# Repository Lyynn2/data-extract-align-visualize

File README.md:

# Setup: Organizing Data

Most scripts have a variable at the beginning called `data_root_dir`.  This should point to a folder that is analogous to the AWS folder `ceti-data > raw > 2023-07-08`.  It should have a subfolder for each device that you want to use, which is named according to the device ID.  

If you want to use coda annotations, the root folder should have subfolders called `_coda_annotations_biology` and `_coda_annotations_haifa` with a CSV in each one; these might be available on AWS, and just in case they're also available [here](https://drive.google.com/drive/folders/1o6aclfZT1td0Xjm15IKLw7Pj57yaxBNU?usp=sharing).

If you want to use the scripts that use extracted files of drone data (`example_use_drone_data.py`, `drone_plot_gps.py`, `drone_plot_speed.py`), you can download the HDF5 files from [here](https://drive.google.com/drive/folders/1VRa-VetmZ5YfDLSZ_6jQgG1d_zl_QoxG?usp=drive_link).  You can then place each one in the relevant drone data subfolder of the data root folder, or adjust the filepaths at the top of the scripts.

# Examples of Extracting Timestamped Data

`example_get_audio_with_timestamps.py` 
- Will load audio data as a raw waveform or as a spectrogram
- Will load aligned timestamps for each audio sample.

`example_get_coda_annotations.py`
- Will load coda annotations from the biology and/or Haifa teams.
- Will provide click times, ICIs, whale indexes, etc. for each coda.
- Timestamps will be adjusted based on alignment offsets.
- **Link to coda annotations files:** [https://drive.google.com/drive/folders/1o6aclfZT1td0Xjm15IKLw7Pj57yaxBNU?usp=sharing](https://drive.google.com/drive/folders/1o6aclfZT1td0Xjm15IKLw7Pj57yaxBNU?usp=sharing)
  - Download the folders from the above link and place them in your root data directory alongside other folders downloaded from AWS.
  - For example, another folder within that root data directory is probably `DSWP-KASHMIR_MIXPRE6-1`
  - `_coda_annotations_biology` and `_coda_annotations_haifa` will be considered the device IDs for now.

`example_use_drone_data.py`
- Will load extracted metadata from HDF5 files.
- Includes GPS positions, altitude, estimated speed, and camera settings for each video frame.
- Includes aligned timestamps for each video frame.
- **Link to drone data files:** [https://drive.google.com/drive/folders/1VRa-VetmZ5YfDLSZ_6jQgG1d_zl_QoxG?usp=drive_link](https://drive.google.com/drive/folders/1VRa-VetmZ5YfDLSZ_6jQgG1d_zl_QoxG?usp=drive_link)
  - Download the two HDF5 files from the `Data and Code` folder. 

# Visualizing Data
`create_composite_video.py` **will create a video with synchronized visualizations from any desired combination of devices.**
  - The dictionary `composite_layout` defines which device streams should be visualized and how they should be arranged on the video.
  - The variables `output_video_start_time_str` and `output_video_duration_s` define the span of the video.

`drone_plot_gps.py` will create an animation of the drones' GPS paths.

 `drone_ploy_speed.py` will plot horizontal drone speed and stationary periods as estimated from the GPS positions.

# Notable Helpers

## Timestamps and Device Alignment

- To get an aligned start time of a file, you can call `adjust_start_time_s(get_time_s_from_filename(filepath), device_id)`
  - `helpers_data_extraction.py > get_time_s_from_filename()` will extract the start time of a file from the 13-digit epoch timestamp in the filename.  This timestamp is from the device clock (not aligned to other devices).
  - `helpers_synchronization.py > adjust_start_time_s()` will adjust a device-based start time to synchronize it with other devices.  Will look up the appropriate offset to add based on the device and the original start time.

- The dictionary `helpers_synchronization.py > epoch_offsets_toAdd_s` defines the manual synchronization offsets.  There may be a single offset per device, or a variable offset per device that changes throughout the expedition.  
  - These were manually defined by finding key frames throughout the data (typically frames when a blow just barely begins).  
  - The hydrophone offset was determined using two codas in file 280 that were also audible in videos.  The file `video_audio_alignment_plotting.py` will plot the waveforms at these codas to visualize the alignment.

- `helpers_various.py > time_s_to_str()` and `time_str_to_time_s()` convert between epoch time (seconds since January 1, 1970) and a human-readable timestamp string.  Note that `time_s_to_str` requires information about the local time zone; for the birthday data `timezone_offset_s = -14400` and `timezone_offset_str = '-0400'`.

## Extracting Timestamped Data
- `helpers_data_extraction.py` provides methods for getting video frames, images, audio waveforms, audio spectrograms, drone flight/camera data, and coda annotations with associated aligned timestamps: 
  - `get_timestamped_data_audioVideoImage()`
  - `get_timestamped_data_codas()` 
  - `get_timestamped_data_drones()` (but note that the HDF5 files mentioned above are recommended, since they include both aligned and original timestamps as well as other formatted fields)

## Subclasses for Faster Video Plotting and Writing

- `ImagePlot` is a custom plotting class to speed up plotting for video generation.  It builds plot images directly instead of using a plotting library, so it is fast for basic functions and does not require a dedicated export/render step to fetch an image of the plot.

- `ThreadedVideoWriter` is a video writer wrapper to speed up video writing.  It maintains a rolling buffer of frames to write and then performs the actual write in a dedicated thread, so your main code can continue working on synthesizing the next frame while the previous frame is being written.

# Python Setup/Installation

The code has so far been run with Python version `3.9.9`. Versions of notable packages that the code has currently been tested with are listed below:

**Image/Video**
- `pip install decord==0.6.0` for quickly loading video frames
- `pip install Pillow==9.1.0` for quickly loading images
- `pip install moviepy==1.0.3` for adding aligned audio to generated composite videos
- `pip install proglog==0.1.10` for controlling log outputs when adding audio to generated composite videos
- `pip install ffmpeg-python==0.2.0` and maybe `pip install ffmpegcv==0.3.7` for compressing output videos
- `pip install opencv-python==4.8.0.76` for drawing text and shapes on images

**Plotting**
- `pip install distinctipy==1.2.2` for generating unique plot colors
- `pip install matplotlib==3.5.1` for plotting drone data
- `pip install tilemapbase==0.4.7` for plotting maps with drone GPS data
- `pip install pyqtgraph==0.12.4` for plotting video/audio alignment graphs. May also be relevant: `pip install PyQt6==6.3.0`, `pip install PyQt6-Qt6==6.3.0`, `pip install PyQt6-sip==13.3.1`, `pip install PyOpenGL==3.1.6`

**Data/Math**
- `pip install numpy==1.23.5`
- `pip install h5py==3.1.0` and maybe `pip install h5py-cache==1.0` for storing/loading extracted drone data
- `pip install pandas==1.3.5` for downloading data from AWS
- `pip install scipy==1.9.1` for loading/processing audio files
- `pip install python-dateutil==2.8.2` for parsing timestamp strings
- `pip install pysrt==1.1.2` for extracting drone data from SRT files

**All of the above**
```
  pip install decord==0.6.0
  pip install Pillow==9.1.0
  pip install moviepy==1.0.3
  pip install proglog==0.1.10
  pip install ffmpeg-python==0.2.0
  pip install ffmpegcv==0.3.7
  pip install opencv-python==4.8.0.76
  pip install distinctipy==1.2.2
  pip install matplotlib==3.5.1
  pip install tilemapbase==0.4.7
  pip install pyqtgraph==0.12.4
  #pip install PyQt6==6.3.0
  #pip install PyQt6-Qt6==6.3.0
  #pip install PyQt6-sip==13.3.1
  #pip install PyOpenGL==3.1.6
  pip install numpy==1.23.5
  pip install h5py==3.1.0
  pip install h5py-cache==1.0
  pip install pandas==1.3.5
  pip install scipy==1.9.1
  pip install python-dateutil==2.8.2
  pip install pysrt==1.1.2
```

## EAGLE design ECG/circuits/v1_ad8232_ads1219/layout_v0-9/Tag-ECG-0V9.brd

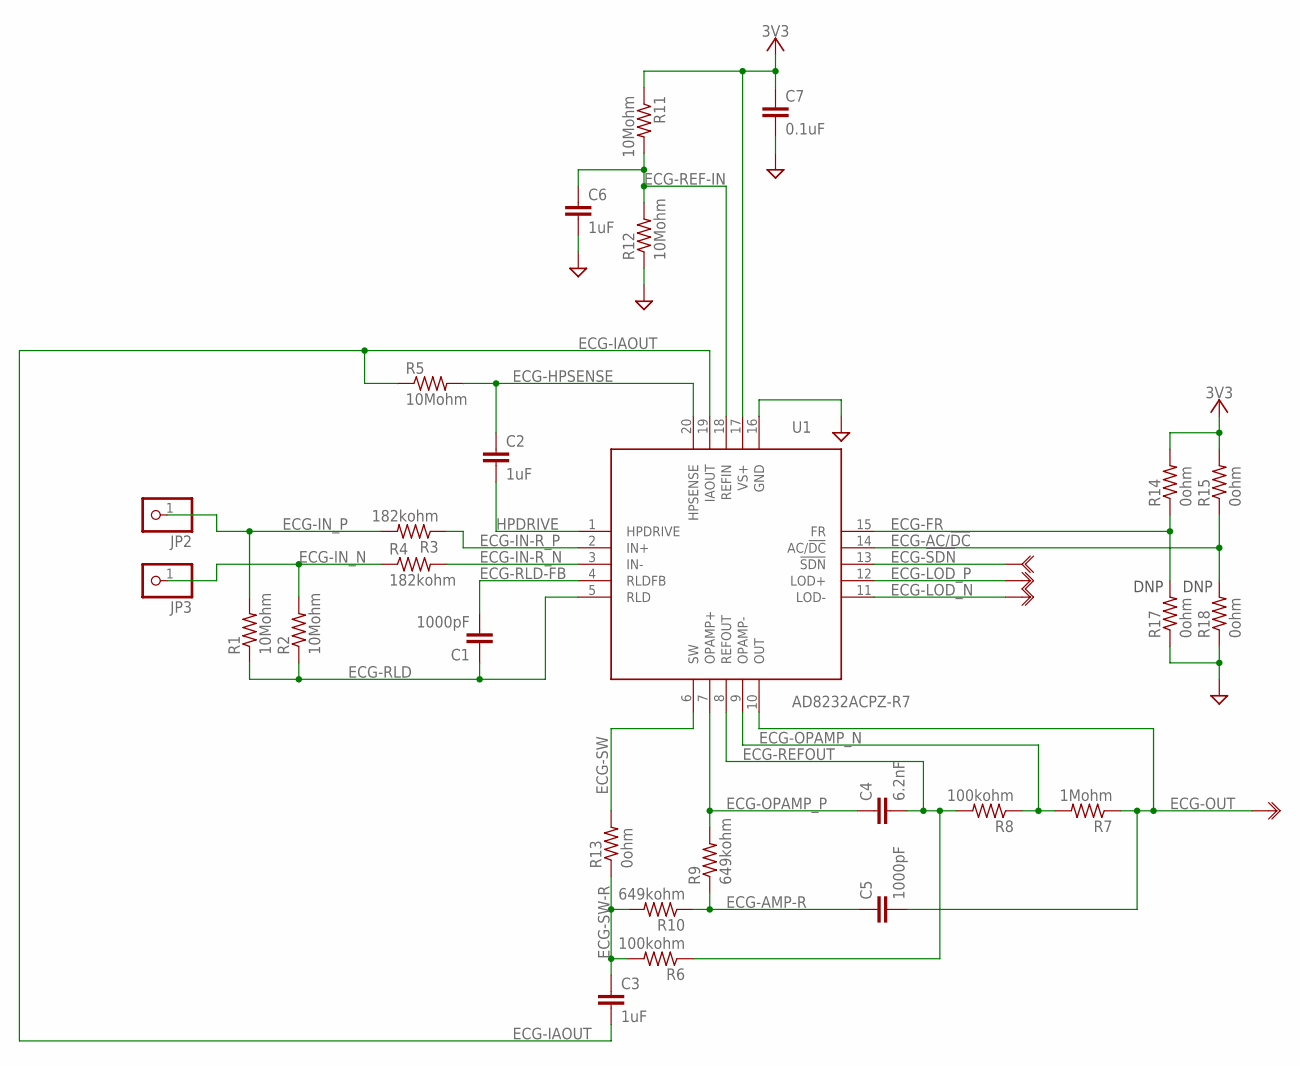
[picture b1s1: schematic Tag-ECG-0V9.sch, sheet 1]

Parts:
C1, C5: 1000pF; C0402
C2, C3, C6: 1uF; C0402
C4: 6.2nF; C0402
C7: 0.1uF; C0402
JP2, JP3: PINHD-1X1; 1X01
R1, R2, R5, R11, R12: 10Mohm; R0402
R3, R4: 182kohm; R0402
R6, R8: 100kohm; R0402
R7: 1Mohm; R0402
R9, R10: 649kohm; R0402
R13, R14, R15, R17, R18: 0ohm; R0402
U1: AD8232ACPZ-R7

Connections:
3V3: C7.1, R11.1, R14.2, R15.2, U1.17 (VS+); also elsewhere on the board
ECG-!SDN: U1.13 (!SDN); also elsewhere on the board
ECG-AC/!DC: R15.1, R18.2, U1.14 (AC/!DC)
ECG-AMP-R: C5.1, R9.1, R10.1
ECG-FR: R14.1, R17.2, U1.15 (FR)
ECG-HPSENSE: C2.1, R5.2, U1.20 (HPSENSE)
ECG-IAOUT: C3.2, R5.1, U1.19 (IAOUT); also elsewhere on the board
ECG-IN-R_N: R4.2, U1.3 (IN-)
ECG-IN-R_P: R3.1, U1.2 (IN+)
ECG-IN_N: JP3.1, R2.2, R4.1; also elsewhere on the board
ECG-IN_P: JP2.1, R1.2, R3.2; also elsewhere on the board
ECG-LOD_N: U1.11 (LOD-); also elsewhere on the board
ECG-LOD_P: U1.12 (LOD+); also elsewhere on the board
ECG-OPAMP_N: R7.2, R8.1, U1.9 (OPAMP-)
ECG-OPAMP_P: C4.1, R9.2, U1.7 (OPAMP+)
ECG-OUT: C5.2, R7.1, U1.10 (OUT); also elsewhere on the board
ECG-REF-IN: C6.1, R11.2, R12.2, U1.18 (REFIN)
ECG-REFOUT: C4.2, R6.1, R8.2, U1.8 (REFOUT)
ECG-RLD: C1.1, R1.1, R2.1, U1.5 (RLD); also elsewhere on the board
ECG-RLD-FB: C1.2, U1.4 (RLDFB)
ECG-SW: R13.2, U1.6 (SW)
ECG-SW-R: C3.1, R6.2, R10.2, R13.1
GND: C6.2, C7.2, R12.1, R17.1, R18.1, U1.16 (GND); also elsewhere on the board
HPDRIVE: C2.2, U1.1 (HPDRIVE)

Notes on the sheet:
DNP

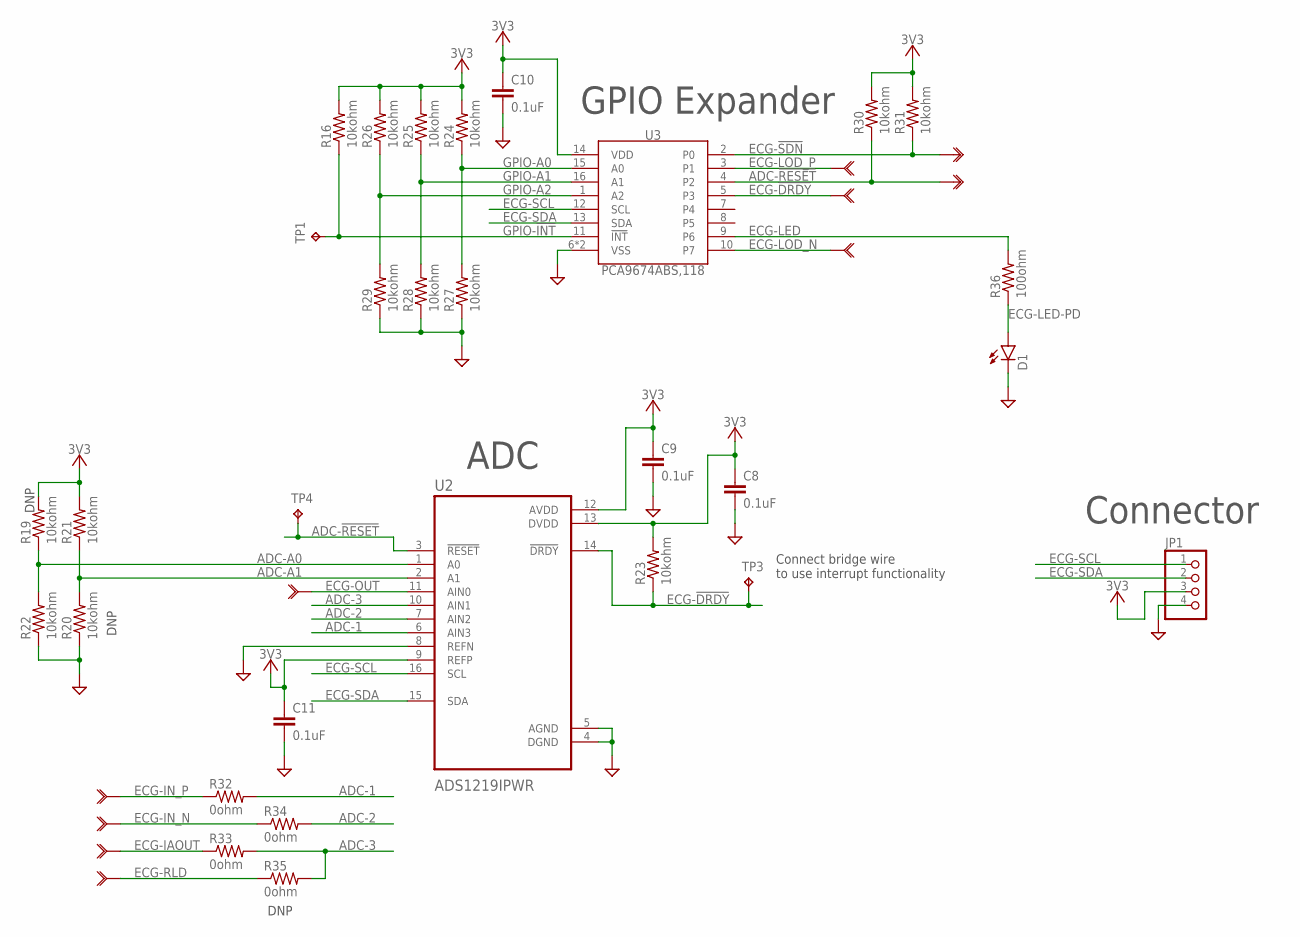
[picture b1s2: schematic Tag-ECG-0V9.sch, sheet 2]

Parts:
C8, C9, C10, C11: 0.1uF; C0402
D1: LED,SMD,GREEN,0603CHIP-LED0603; CHIP-LED0603
JP1: PINHD-1X4; 1X04
R16, R19, R20, R21, R22, R23, R24, R25, R26, R27, R28, R29, R30, R31: 10kohm; R0402
R32, R33, R34, R35: 0ohm; R0402
R36: 100ohm; R0402
TP1, TP3, TP4: TPB1,27; B1,27
U2: ADS1219IPWR; SOP65P640X120-16N
U3: PCA9674ABS,118

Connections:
3V3: C8.1, C9.1, C10.1, C11.1, JP1.3, R16.2, R19.2, R21.2, R23.2, R24.2, R25.2, R26.2, R30.2, R31.2, U2.9 (REFP), U2.12 (AVDD), U2.13 (DVDD), U3.14 (VDD); also elsewhere on the board
ADC-1: R32.2, U2.6 (AIN3)
ADC-2: R34.2, U2.7 (AIN2)
ADC-3: R33.2, R35.2, U2.10 (AIN1)
ADC-!RESET: R30.1, TP4.TP, U2.3 (!RESET), U3.4 (P2)
ADC-A0: R19.1, R22.2, U2.1 (A0)
ADC-A1: R20.2, R21.1, U2.2 (A1)
ECG-!DRDY: R23.1, TP3.TP, U2.14 (!DRDY), U3.5 (P3)
ECG-!SDN: R31.1, U3.2 (P0); also elsewhere on the board
ECG-IAOUT: R33.1; also elsewhere on the board
ECG-IN_N: R34.1; also elsewhere on the board
ECG-IN_P: R32.1; also elsewhere on the board
ECG-LED: R36.2, U3.9 (P6)
ECG-LED-PD: D1.A, R36.1
ECG-LOD_N: U3.10 (P7); also elsewhere on the board
ECG-LOD_P: U3.3 (P1); also elsewhere on the board
ECG-OUT: U2.11 (AIN0); also elsewhere on the board
ECG-RLD: R35.1; also elsewhere on the board
ECG-SCL: JP1.1, U2.16 (SCL), U3.12 (SCL)
ECG-SDA: JP1.2, U2.15 (SDA), U3.13 (SDA)
GND: C8.2, C9.2, C10.2, C11.2, D1.C, JP1.4, R20.1, R22.1, R27.1, R28.1, R29.1, U2.4 (DGND), U2.5 (AGND), U2.8 (REFN), U3.6 (VSS), U3.17 (VSS); also elsewhere on the board
GPIO-!INT: R16.1, TP1.TP, U3.11 (!INT)
GPIO-A0: R24.1, R27.2, U3.15 (A0)
GPIO-A1: R25.1, R28.2, U3.16 (A1)
GPIO-A2: R26.1, R29.2, U3.1 (A2)

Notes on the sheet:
DNP
Connect bridge wire to use interrupt functionality
ADC
GPIO Expander
Connector

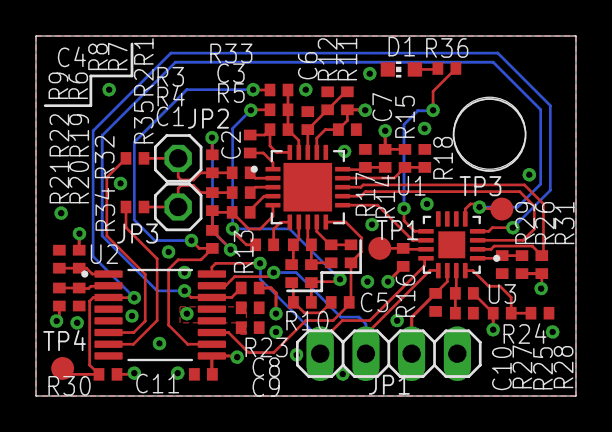
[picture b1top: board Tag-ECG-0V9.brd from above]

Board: 4 copper layers, 30.0 x 20.0 mm, 57 parts (0 on the bottom side), 39 nets.

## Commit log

2023-08-07 Happy birthday! Creating a composite video of the birthday data. -- Extracts timestamps for every device. -- Finds the best device timestamp for each output video timestamp. -- Shows images/frames, a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
2023-08-08 Cleaning/organizing script to generate the composite video.
2023-08-09 Speed up image loading and frame updating; generate shared video. -- Only fetch data and update a layout if the data has changed since the previous frame; this avoids re-loading images every frame. -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
2023-08-09 Automatically align and add audio tracks; compress the output composite video. -- Automatically add the audio track to the composite video. ---- Search for audio files that overlap with the video, an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
2023-08-10 Speed up video reading by using Decorder. -- Use Decorder to read videos; in dedicated tests, this was about 30x faster than OpenCV. -- Allow Decorder to resize the video frames as they are read, rat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
2023-08-11 Using OpenCV to do the layout directly instead of PyQtGraph subplots. -- Generated the video on 2023-08-10.
2023-08-11 Fixing the shape of image dummy data. -- Getting a blank image that fills the entire subplot, rather than only the size of the example image. ---- This ensures that it will be cleared correctly if th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
2023-08-11 Plotting an audio spectrogram instead of the audio waveform [initial updates]. -- In a 2-second test, seems to speed up overall frame rate from 2.0 fps (using 9.6k waveform) to 3.1 fps (using 96k spe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
2023-08-11 Speeding up spectrogram plotting for the composite video. -- Compute the spectrogram of the entire audio file at once instead of for each buffer, and then scroll through the larger matrix. -- Adjusti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
2023-08-13 Aligning the hydrophone to a phone video using Shane's coda. -- Plotting the hydrophone and phone audio to refine the alignment. -- Generating a spectrogram version and a waveform version.
2023-08-15 Updating alignment offsets; updating spectrogram formatting. -- Attempting an automatic alignment of audio using cross correlation, but seems to not find the best position. -- Adding an option for wh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
2023-08-15 Fixed manual alignment offsets. -- Updating manual alignment offsets by using actual frame rates instead of rounded Premiere frame rates. -- PyCharm formatted some whitespace when pasting the entire 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
2023-08-16 Extract drone frame timestamps from SRT files. -- Also expand the allowable window for matching device frames with the current time.
2023-08-16 Create a visualization of position data from all drones. -- Visualize drone position data; show markers at the latitude/longitude of each drone, and color the markers according to altitude. -- Genera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
2023-08-16 Enhancing drone position visualization. -- Convert latitude and longitude to meters. -- Dynamically update the plot range to follow the drones. -- Adjust the grid spacing and formatting. -- Add a col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
2023-08-17 Drone visualization updates; subplot label updates; various small updates. -- Optionally add the audio track to the original video as well as to the compressed video. -- Optionally delete the output 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
2023-08-18 Align the Pixel5 and GoPro devices to drones based on manual key frames.
2023-08-18 Visualization formatting updates. -- Update the drone visualization formatting. ---- Outline the drone labels in the appropriate color instead of changing the whole background or the text color. ----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
2023-08-28 Visualize annotated codas. -- Visualize codas by plotting each click's inter-click interval and color-coding by whale index. ---- Extract the data from a CSV of manual annotations provided by the bio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
2023-08-28 Small updates for spectrogram windows and coda annotation extractions. -- Ensure that spectrogram window sizes are the same across files. -- Store coda end times in addition to coda start times.
2023-08-28 Work in progress; attempt speedup by only plotting visible codas. -- Speed seems to be largely unchanged from the version that plots all codas but changes the x range.
2023-08-28 Adding an alternative coda visualization based on exchange plots. -- Can optionally plot each click at its time since the coda start, instead of at its subsequent ICI. -- Renamed variables to use "co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
2023-08-29 Allow multiple epoch offsets per device for more granular alignment; update drone and T5i offsets. -- Can specify the epoch time until which a given offset applies to a device. -- Manually adjust dro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
2023-09-04 Using a custom plotting class to speed up coda visualizations. -- Create the ImagePlot class to make graphs directly on images; this significantly improves plotting speed and avoids plot exporting. -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
2023-09-04 Creating a threaded buffered video writer to improve speed. -- Storing a buffer of frames to write and then processing them in a dedicated thread, so the main thread does not need to wait for writing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
2023-09-06 Major cleaning and organizing; some optimizations. -- Cleaning, organizing, commenting, and pruning all files. -- Restructuring some logical flows. -- Making adjustments along the way to reduce proce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
2023-09-06 Small updates to drone plotting, ImagePlot ticks, and printouts. -- Adjust how tick spacings are computed to better accommodate numeric imprecisions; previously had the wrong number of ticks due to r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
2023-09-11 Allowing for multiple sources of coda annotations; adding Haifa annotations. -- Generated video that was shared on YouTube on 2023-09-09.
2023-09-12 Updating when coda plots appear and disappear. -- Recording the start/end times of each annotated audio file within the single annotations file. -- Used to generate video with Haifa annotations that 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
2023-09-24 Organizing and cleaning code. -- Creating multiple files of helper functions. -- Creating an example script for getting audio data and timestamps. -- Moving test files to a separate directory. -- Gen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
2023-09-26 Initial versions of extracting and using drone metadata including GPS. -- Save drone metadata from the SRT files to dedicated HDF5 files. -- Animate the drone GPS paths over time. -- Estimate drone s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
2023-09-26 Organizing and cleaning drone data processing scripts. -- Include datasets of estimated speed and stationary times in the HDF5 files. -- Create helper functions for moving averages, finding rising ed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
2023-09-27 Drone processing updates; some general cleaning and organizing. -- Estimating vertical drone speed using altitude in addition to horizontal speed using GPS. -- Adding an example of re-estimating dron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
2023-09-27 Adding a ReadMe; updating coda annotation extraction; some general cleaning/organizing. -- Adding an example script of getting coda annotations for both Biology and Haifa sources. -- Updating the def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
2023-09-27 Organizing/cleaning; removing test files.
2023-09-28 Preparing to push to new repository; removing non-birthday files.
2023-09-28 Moving all files to the root of the repository.
2023-09-28 Updating the ReadMe with a section about organizing data.
